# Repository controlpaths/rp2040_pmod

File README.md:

# RP2040 PMOD

The RP2040 PMOD is a PMOD-compatible board based on the [Raspberry PI](https://www.raspberrypi.com/) microcontroller, the [RP2040](https://www.raspberrypi.com/products/rp2040/)

The board has its own 3v3 LDO regulator, and the 3v3 pins of the PMOD connector are not connected.

PMOD connector.

## PMOD Connections

|PMOD PIN|Schematic|GPIO|Fuction|
|-|-|-|-|
|1|NC|--|--|
|2|NC|--|--|
|3|GND|--|GND|
|4|GND|--|GND|
|5|PMOD5|20|SPI0 RX / UART1 TX / I2C0 SDA|
|6|PMOD6|21|SPI0 CSn / UART1 RX / I2C0 SCL|
|7|PMOD3|18|SPI0 SCK / UART0 CTS / I2C1 SDA|
|8|PMOD4|19|SPI0 TX / UART0 RTS / I2C1 SCL|
|9|PMOD1|16|SPI0 RX / UART0 TX / I2C0 SDA|
|10|PMOD2|17|SPI0 CSn / UART0 RX / I2C0 SCL|
|11|UART_TX|0|SPI0 RX / UART0 TX / I2C0 SDA|
|12|UART_RX|1|SPI0 CSn / UART0 RX / I2C0 SCL|

## Examples

On the `/examples` folder you will find examples to program in this board. 

- [pico-uart-bridge](./examples/pico-uart-bridge/): Uses the RP2040 PMOD to generate two different UART interfaces in the PMOD PINS 5/6 and 11/12.

More examples soon!

## Get Yours

The RP2040 PMOD is open-source, so you can use the output files to manufacture your own in [JLCPCB](https://jlcpcb.com/?from=controlpath). You just need to compress the `output_files` directory, and upload it to [JLCPCB](https://jlcpcb.com/?from=controlpath). 

Remember to change the Surface Finish to **LeadFree HASL** to make your board ROHS compliant.

Then you have to add the PCB Assembly service and upload the [centroid](./kicad/output_files/rp2040_pmod-all-pos.csv) file, and the [BOM](./kicad/output_files/bom.csv). 

In a few days, you will receive your board at home. If you want just one RP2040 PMOD, contact me.

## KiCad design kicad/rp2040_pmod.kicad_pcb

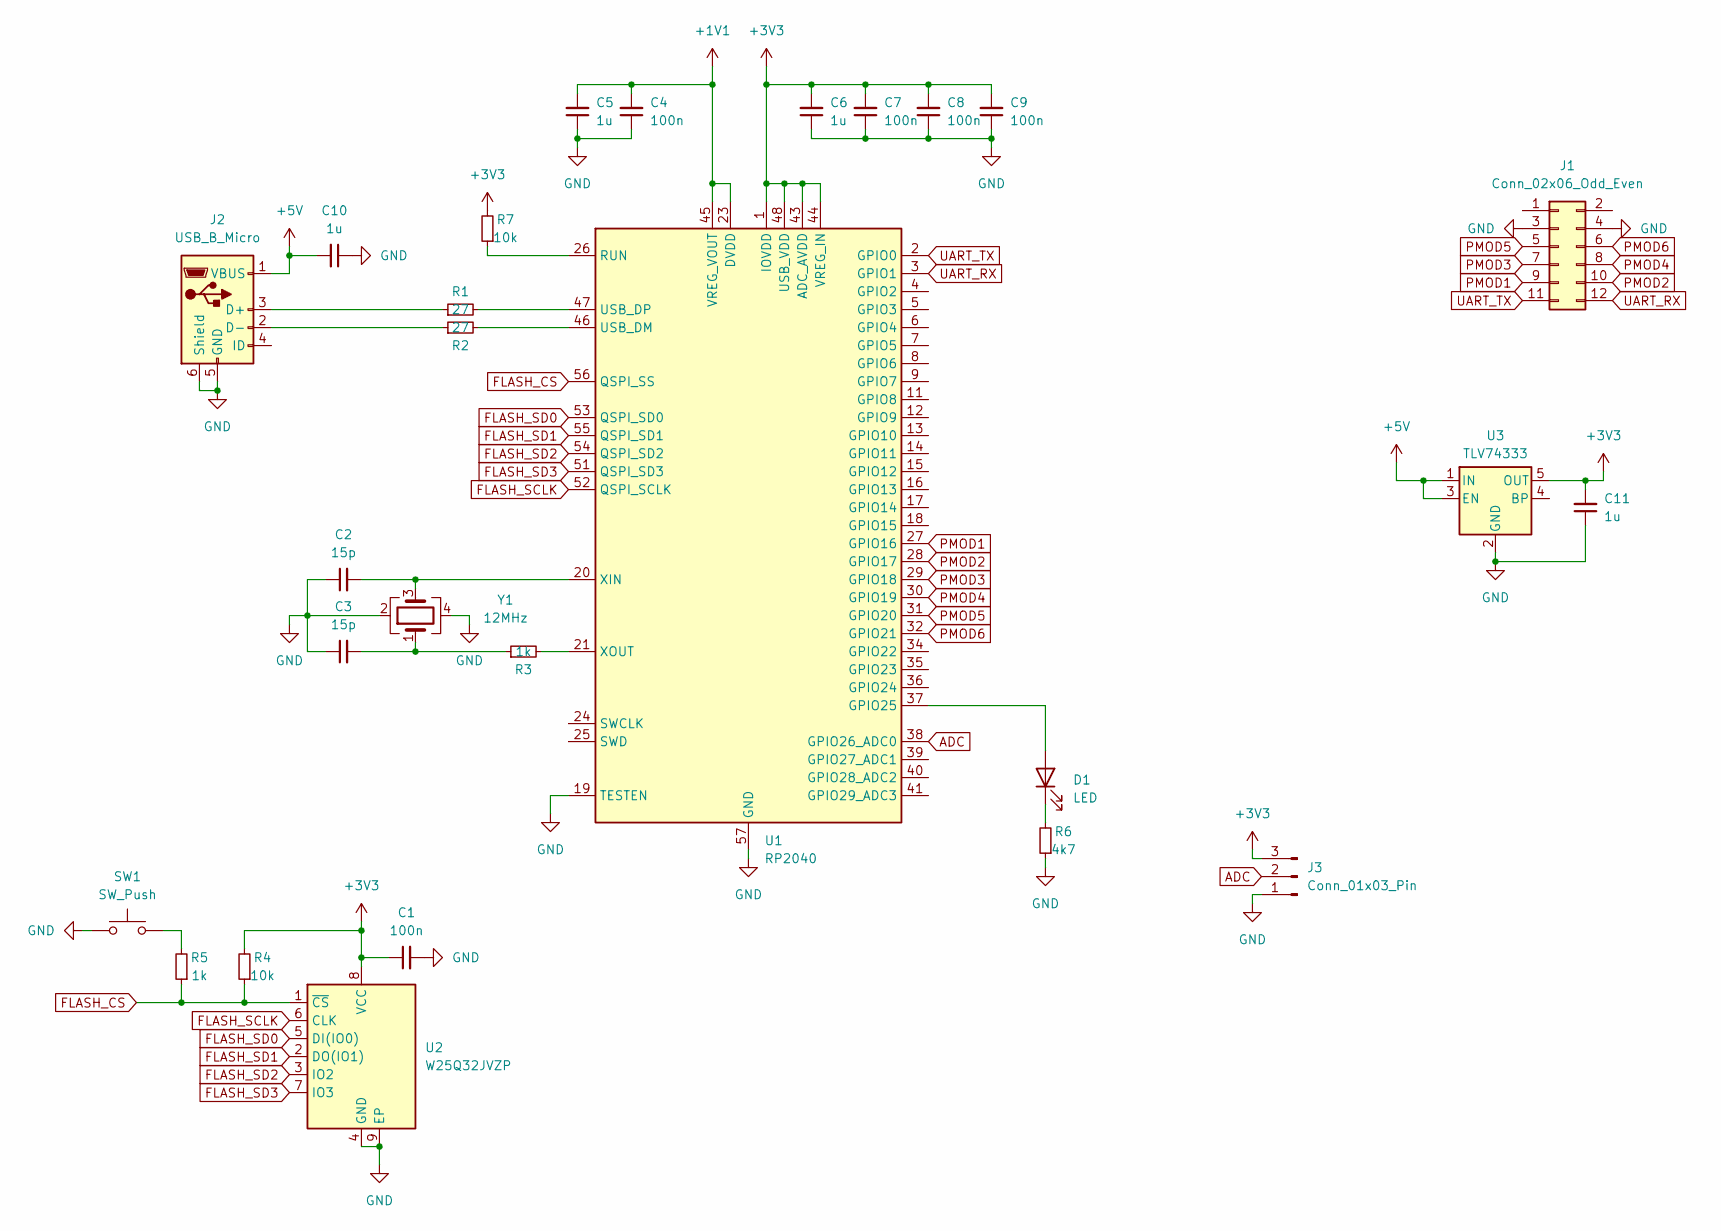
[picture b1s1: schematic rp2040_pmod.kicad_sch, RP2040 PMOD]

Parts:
C1, C4, C7, C8, C9: 100n; C_0603_1608Metric
C2, C3: 15p; C_0603_1608Metric
C5, C6, C10, C11: 1u; C_0603_1608Metric
D1: LED; LED_0603_1608Metric
J1: Conn_02x06_Odd_Even; PinHeader_2x06_P2.54mm_Horizontal
J2: USB_B_Micro; USB_Micro-B_Amphenol_10118193-0001LF_Horizontal; JLCPCB Part # C132562
J3: Conn_01x03_Pin; PinHeader_1x03_P2.54mm_Vertical
R1, R2: 27; R_0603_1608Metric
R3, R5: 1k; R_0603_1608Metric
R4, R7: 10k; R_0603_1608Metric
R6: 4k7; R_0603_1608Metric
SW1: SW_Push; SW_Push_SPST_NO_Alps_SKRK; JLCPCB Part # C115357
U1: RP2040; QFN-56-1EP_7x7mm_P0.4mm_EP3.2x3.2mm
U2: W25Q32JVZP; WSON-8-1EP_6x5mm_P1.27mm_EP3.4x4.3mm; JLCPCB Part # C2940197
U3: TLV74333; SOT-23-5; JLCPCB Part # C408972
Y1: 12MHz; Crystal_SMD_3225-4Pin_3.2x2.5mm; JLCPCB Part # C524716

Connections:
+1V1: C4.2, C5.2, U1.23 (DVDD), U1.45 (VREG_VOUT), U1.50 (DVDD)
+3V3: C1.1, C6.2, C7.2, C8.2, C9.2, C11.2, J3.3, R4.2, R7.2, U1.1 (IOVDD), U1.10 (IOVDD), U1.22 (IOVDD), U1.33 (IOVDD), U1.42 (IOVDD), U1.43 (ADC_AVDD), U1.44 (VREG_IN), U1.48 (USB_VDD), U1.49 (IOVDD), U2.8 (VCC), U3.5 (OUT)
+5V: C10.2, J2.1 (VBUS), U3.1 (IN), U3.3 (EN)
ADC: J3.2, U1.38 (GPIO26_ADC0)
FLASH_CS: R4.1, R5.1, U1.56 (QSPI_SS), U2.1 (~CS)
FLASH_SCLK: U1.52 (QSPI_SCLK), U2.6 (CLK)
FLASH_SD0: U1.53 (QSPI_SD0), U2.5 (DI(IO0))
FLASH_SD1: U1.55 (QSPI_SD1), U2.2 (DO(IO1))
FLASH_SD2: U1.54 (QSPI_SD2), U2.3 (IO2)
FLASH_SD3: U1.51 (QSPI_SD3), U2.7 (IO3)
GND: C1.2, C2.1, C3.1, C4.1, C5.1, C6.1, C7.1, C8.1, C9.1, C10.1, C11.1, J1.3, J1.4, J2.5 (GND), J2.6 (Shield), J3.1, R6.1, SW1.1, U1.19 (TESTEN), U1.57 (GND), U2.4 (GND), U2.9 (EP), U3.2 (GND), Y1.2, Y1.4
unnamed: C3.2, R3.1, Y1.1
unnamed: D1.2 (A), U1.37 (GPIO25)
unnamed: D1.1 (K), R6.2
unnamed: J2.3 (D+), R1.1
unnamed: J2.2 (D-), R2.1
unnamed: R5.2, SW1.2
unnamed: R7.1, U1.26 (RUN)
unnamed: R2.2, U1.46 (USB_DM)
unnamed: R1.2, U1.47 (USB_DP)
unnamed: C2.2, U1.20 (XIN), Y1.3
unnamed: R3.2, U1.21 (XOUT)
PMOD1: J1.9, U1.27 (GPIO16)
PMOD2: J1.10, U1.28 (GPIO17)
PMOD3: J1.7, U1.29 (GPIO18)
PMOD4: J1.8, U1.30 (GPIO19)
PMOD5: J1.5, U1.31 (GPIO20)
PMOD6: J1.6, U1.32 (GPIO21)
UART_RX: J1.12, U1.3 (GPIO1)
UART_TX: J1.11, U1.2 (GPIO0)

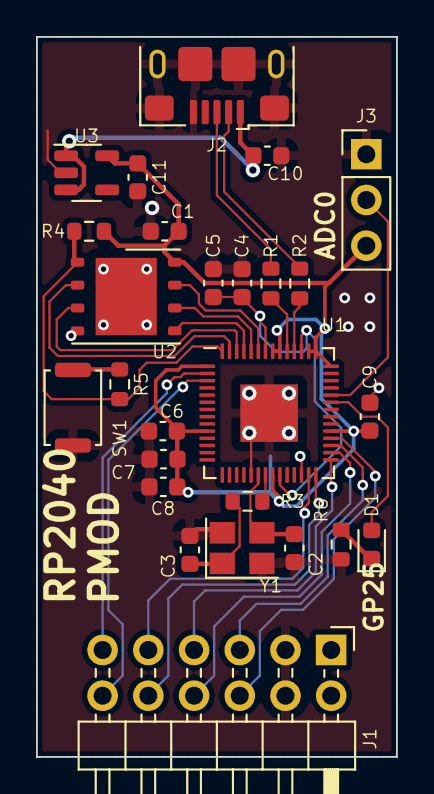
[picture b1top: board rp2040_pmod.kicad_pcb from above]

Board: 2 copper layers, 20.0 x 40.0 mm, 27 parts (1 on the bottom side), 30 nets.

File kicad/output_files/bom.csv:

"#","Reference","Qty","Value","Footprint","DNP","JLCPCB Part #"
"1","C1, C4, C7, C8, C9","5","100n","Capacitor_SMD:C_0603_1608Metric","",""
"2","C2, C3","2","15p","Capacitor_SMD:C_0603_1608Metric","",""
"3","C5, C6, C10, C11","4","1u","Capacitor_SMD:C_0603_1608Metric","",""
"4","D1","1","LED","LED_SMD:LED_0603_1608Metric","",""
"5","J1","1","Conn_02x06_Odd_Even","Connector_PinHeader_2.54mm:PinHeader_2x06_P2.54mm_Horizontal","",""
"6","J2","1","USB_B_Micro","Connector_USB:USB_Micro-B_Amphenol_10118193-0001LF_Horizontal","","C132562"
"7","J3","1","Conn_01x03_Pin","Connector_PinHeader_2.54mm:PinHeader_1x03_P2.54mm_Vertical","",""
"8","R1, R2","2","27","Resistor_SMD:R_0603_1608Metric","",""
"9","R3, R5","2","1k","Resistor_SMD:R_0603_1608Metric","",""
"10","R4, R7","2","10k","Resistor_SMD:R_0603_1608Metric","",""
"11","R6","1","4k7","Resistor_SMD:R_0603_1608Metric","",""
"12","SW1","1","SW_Push","Button_Switch_SMD:SW_Push_SPST_NO_Alps_SKRK","","C115357"
"13","U1","1","RP2040","Package_DFN_QFN:QFN-56-1EP_7x7mm_P0.4mm_EP3.2x3.2mm","",""
"14","U2","1","W25Q32JVZP","Package_SON:WSON-8-1EP_6x5mm_P1.27mm_EP3.4x4.3mm","","C2940197"
"15","U3","1","TLV74333","Package_TO_SOT_SMD:SOT-23-5","","C408972"
"16","Y1","1","12MHz","Crystal:Crystal_SMD_3225-4Pin_3.2x2.5mm","","C524716"

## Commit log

2023-12-23 uploaded kicad files of the first version
2023-12-23 added pico-uart-bridge example as a submodule
2023-12-24 updated example
2024-01-02 fixed gitignore to add bom and pos file
